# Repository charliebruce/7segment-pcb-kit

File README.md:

# 7segment-pcb-kit
Eagle design files for 7-segment PCB kit. This kit is designed to offer a gentle introduction to soldering, DIP switches, 7-segment displays, and can tie in with lesson(s) regarding basic encryption methods - the "keys" attached can change the connections between switches and segments.

# License
Released under the CC BY-NC-SA 3.0 license.

For more details see a summary at: https://creativecommons.org/licenses/by-nc-sa/3.0/ and the accompanying legal text: https://creativecommons.org/licenses/by-nc-sa/3.0/legalcode

Please raise an issue or send me an email if you wish to use this project commercially.

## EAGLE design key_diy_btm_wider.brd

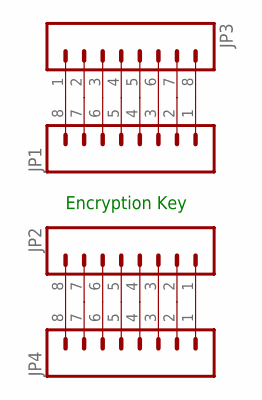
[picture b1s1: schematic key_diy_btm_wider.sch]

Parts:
JP1, JP2: M08LOCK; 1X08_LOCK
JP3, JP4: M08LONGPADS; 1X08_LONGPADS

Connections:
unnamed: JP1.1, JP3.8
unnamed: JP1.2, JP3.7
unnamed: JP1.3, JP3.6
unnamed: JP1.4, JP3.5
unnamed: JP1.5, JP3.4
unnamed: JP1.6, JP3.3
unnamed: JP1.7, JP3.2
unnamed: JP1.8, JP3.1
unnamed: JP2.1, JP4.1
unnamed: JP2.2, JP4.2
unnamed: JP2.3, JP4.3
unnamed: JP2.4, JP4.4
unnamed: JP2.5, JP4.5
unnamed: JP2.6, JP4.6
unnamed: JP2.7, JP4.7
unnamed: JP2.8, JP4.8

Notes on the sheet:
Encryption Key

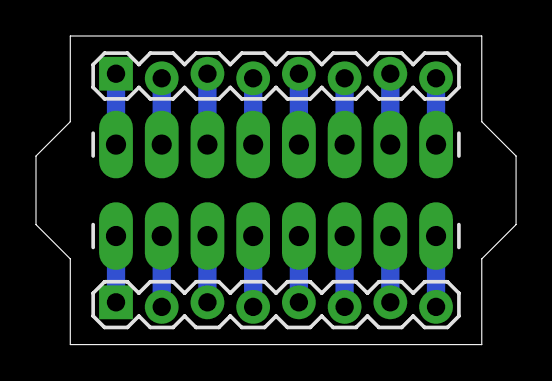
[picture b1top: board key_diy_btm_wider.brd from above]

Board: 2 copper layers, 26.7 x 17.1 mm, 4 parts (0 on the bottom side), 16 nets.

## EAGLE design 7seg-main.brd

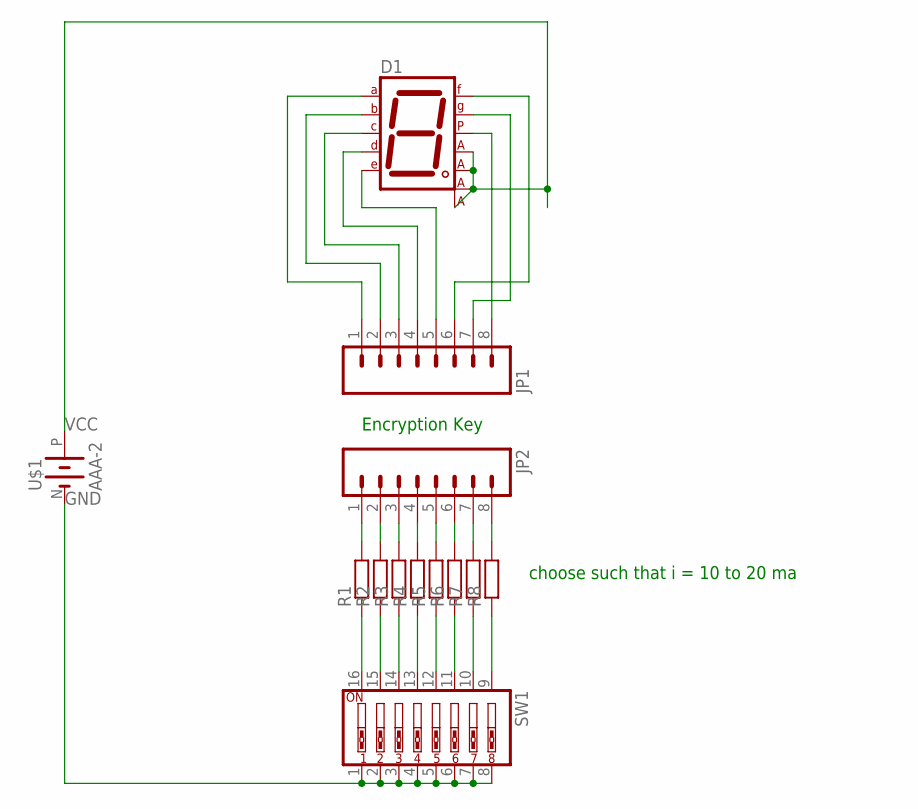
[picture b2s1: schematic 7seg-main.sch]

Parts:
D1: 7SEG-CA-204; 7SEG-0.8IN
JP1, JP2: M08LOCK_LONGPADS; 1X08_LOCK_LONGPADS
R1, R2, R3, R4, R5, R6, R7, R8: RESISTOR_0207/10; 0207/10
SW1: SW_DIP-8; EDG-08
U$1: AAA-2; AA-2

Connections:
GND: SW1.1, SW1.2, SW1.3, SW1.4, SW1.5, SW1.6, SW1.7, SW1.8, U$1.N (-)
unnamed: R1.1, SW1.16
unnamed: D1.9 (DP), JP1.8
unnamed: JP2.1, R1.2
unnamed: JP2.2, R2.2
unnamed: JP2.3, R3.2
unnamed: JP2.4, R4.2
unnamed: JP2.5, R5.2
unnamed: JP2.6, R6.2
unnamed: JP2.7, R7.2
unnamed: JP2.8, R8.2
unnamed: R2.1, SW1.15
unnamed: R3.1, SW1.14
unnamed: R4.1, SW1.13
unnamed: R5.1, SW1.12
unnamed: R6.1, SW1.11
unnamed: R7.1, SW1.10
unnamed: R8.1, SW1.9
unnamed: D1.13 (G), JP1.7
unnamed: D1.2 (F), JP1.6
unnamed: D1.4 (E), JP1.5
unnamed: D1.10 (D), JP1.4
unnamed: D1.12 (C), JP1.3
unnamed: D1.14 (B), JP1.2
unnamed: D1.1 (A), JP1.1
VCC: D1.3 (CA1), D1.5 (CA2), D1.11 (CA3), D1.16 (CA4), U$1.P (+)

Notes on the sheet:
Encryption Key
choose such that i = 10 to 20 ma

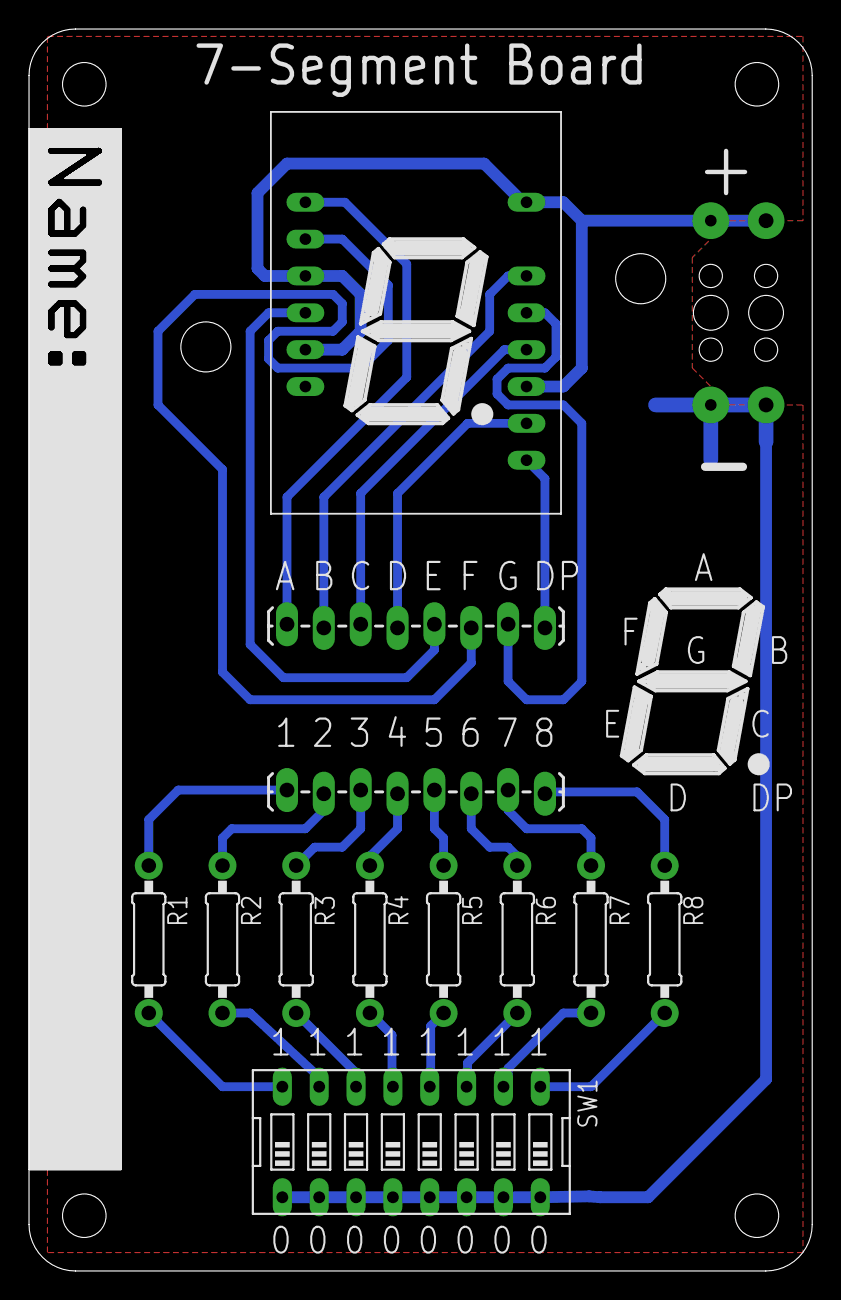
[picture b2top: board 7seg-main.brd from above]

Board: 2 copper layers, 54.0 x 85.6 mm, 13 parts (1 on the bottom side), 26 nets.

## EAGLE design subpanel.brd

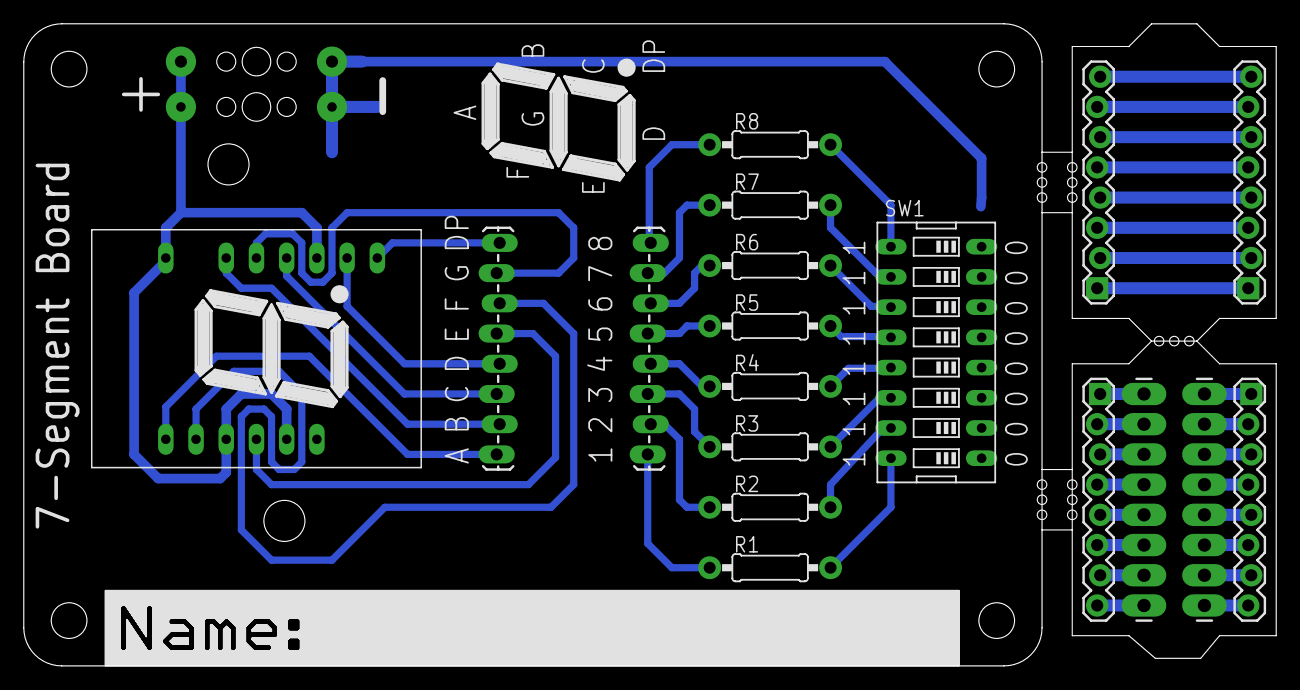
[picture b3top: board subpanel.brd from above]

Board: 2 copper layers, 105.3 x 54.0 mm, 19 parts (1 on the bottom side), 50 nets.

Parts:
D1: 7SEG-0.8IN
JP1, JP2, JP7, JP8: 1X08_LOCK
JP3, JP4: 1X08_LONGPADS
JP5, JP6: 1X08_LOCK_LONGPADS
R1, R2, R3, R4, R5, R6, R7, R8: 0207/10
SW1: EDG-08
U$1: AAA-2; AA-2

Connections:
GND: SW1.1, SW1.2, SW1.3, SW1.4, SW1.5, SW1.6, SW1.7, SW1.8, U$1.N
unnamed: JP1.1, JP3.8
unnamed: JP1.2, JP3.7
unnamed: JP1.3, JP3.6
unnamed: JP1.4, JP3.5
unnamed: JP1.5, JP3.4
unnamed: JP1.6, JP3.3
unnamed: JP1.7, JP3.2
unnamed: JP1.8, JP3.1
unnamed: JP2.1, JP4.1
unnamed: JP2.2, JP4.2
unnamed: JP2.3, JP4.3
unnamed: JP2.4, JP4.4
unnamed: JP2.5, JP4.5
unnamed: JP2.6, JP4.6
unnamed: JP2.7, JP4.7
unnamed: JP2.8, JP4.8
unnamed: JP6.1, R1.2
unnamed: JP6.2, R2.2
unnamed: JP6.3, R3.2
unnamed: JP6.4, R4.2
unnamed: JP6.5, R5.2
unnamed: JP6.6, R6.2
unnamed: JP6.7, R7.2
unnamed: JP6.8, R8.2
unnamed: D1.9, JP5.8
unnamed: D1.13, JP5.7
unnamed: D1.2, JP5.6
unnamed: D1.4, JP5.5
unnamed: D1.10, JP5.4
unnamed: D1.12, JP5.3
unnamed: D1.14, JP5.2
unnamed: D1.1, JP5.1
unnamed: R1.1, SW1.16
unnamed: R2.1, SW1.15
unnamed: R3.1, SW1.14
unnamed: R4.1, SW1.13
unnamed: R5.1, SW1.12
unnamed: R6.1, SW1.11
unnamed: R7.1, SW1.10
unnamed: R8.1, SW1.9
unnamed: JP7.8, JP8.8
unnamed: JP7.7, JP8.7
unnamed: JP7.6, JP8.6
unnamed: JP7.5, JP8.5
unnamed: JP7.4, JP8.4
unnamed: JP7.3, JP8.3
unnamed: JP7.2, JP8.2
unnamed: JP7.1, JP8.1
VCC: D1.3, D1.5, D1.11, D1.16, U$1.P

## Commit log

2015-09-05 Initial commit of 7-segment project.
2017-04-30 Add board render image
2017-04-30 Embed image into README
2017-05-01 Set theme jekyll-theme-slate
2017-05-01 Change transparency, tidy up 7-segment graphic

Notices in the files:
parts and their libraries:
SparkFun-Connectors: Licensing: CC v3.0 Share-Alike You are welcome to use this library for commercial purposes.
